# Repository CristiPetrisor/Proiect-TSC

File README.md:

# OpenBook E-Reader - Readme

**Proiect TSC - Caramida-Stoian Petrisor-Cristian**

## Prezentare pe scurt

OpenBook este un e-reader open-source bazat pe ESP32-C6, dotat cu ecran e-paper de 7.5", senzori de mediu, sistem de alimentare cu baterie și conectivitate Wi-Fi și USB-C. Documentul prezintă structura hardware și componentele integrate.

## Diagramă Bloc

```
           +-------------------------+
           |         Battery          |
           +------------+------------+
                        |
                        v
           +-------------------------+
           |     Charging IC (USB-C)  |
           +------------+------------+
                        |
                        v
           +-------------------------+
           |         LDO              |  ---> 3.3V
           +------------+------------+
                        |
     +------------------+-------------------+------------------+
     |                  |                   |                  |
     v                  v                   v                  v
+------------+   +--------------+   +---------------+   +-----------------+
|   ESP32    |<->|    Display   |<->|    BME688     |<->|  Tactile Buttons|
|    -C6     |   |   (SPI: 4W)   |   |   (I2C Bus)   |   |   (GPIO + RC)   |
+------------+   +--------------+   +---------------+   +-----------------+
     |                  ^                    ^                    ^
     |                  |                    |                    |
     |                  |              Pull-up Resistors     Debouncing RC
     |                  |
     v                  |
+----------------------------+
|      USB-C Connector       |
| (USB Data ↔ ESP32 USB)     |
| (ESD & Termination Prot.)  |
+----------------------------+
```

## Lista BOM

| **Componentă**       | **Part Number**               | **Descriere**                          | **Furnizor (Mouser)**                                                               | **Datasheet**                                                                                 |
|----------------------|------------------------------|----------------------------------------|------------------------------------------------------------------------------------|----------------------------------------------------------------------------------------------|
| 1         | ADAFRUIT_LEDCHIP-LED0603           | -       | LED                                       | ADAFRUIT_CHIP-LED0603           | CHG_LED      | [link](https://www.mouser.com/ProductDetail/Adafruit/CHIP-LED0603)               | [datasheet](https://www.mouser.com/datasheet/2/737/CHIP-LED0603-1877199.pdf)       |
| 1         | SJ                                 | -       | SMD solder JUMPER                         | SJ                              | SJ1          | [link](https://www.mouser.com/ProductDetail/TE-Connectivity/1-2176091-2)         | [datasheet](https://www.mouser.com/datasheet/2/418/1-2176091-2-1817091.pdf)        |
| 1         | ESP32_WROVER_EAGLE-LTSPICE_RR0402  | 0.47Ω   | Rezistor                                  | ESP32_WROVER_EAGLE-LTSPICE_R0402| R3           | [link](https://www.mouser.com/ProductDetail/Vishay/CRCW04020047ZRT7)             | [datasheet](https://www.mouser.com/datasheet/2/427/crcwce-1764191.pdf)             |
| 1         | ESP32_WROVER_EAGLE-LTSPICE_RR0402  | 100KΩ   | Rezistor                                  | ESP32_WROVER_EAGLE-LTSPICE_R0402| R1_PWRUSB    | [link](https://www.mouser.com/ProductDetail/Vishay/CRCW0402100KFKED)             | [datasheet](https://www.mouser.com/datasheet/2/427/crcwce-1764191.pdf)             |
| 8         | EAGLE-LTSPICE_CC0402               | 100nF   | Condensator                               | EAGLE-LTSPICE_C0402             | C1, C2, C4_USB, C6, C8, C9, C10, C_DELAY | [link](https://www.mouser.com/ProductDetail/Murata/GRM155R71C104KA88D)            | [datasheet](https://www.mouser.com/datasheet/2/281/GRM155R71C104KA88D-1767201.pdf) |
| 1         | RCL_CPOL-EUCT3528                  | 100µF   | Condensator polarizat                     | RCL_CT3528                      | C3           | [link](https://www.mouser.com/ProductDetail/Panasonic/EEE-FK1V101P)              | [datasheet](https://www.mouser.com/datasheet/2/315/EEE-FK1V101P-1526881.pdf)       |
| 10        | ESP32_WROVER_EAGLE-LTSPICE_RR0402  | 10KΩ    | Rezistor                                  | ESP32_WROVER_EAGLE-LTSPICE_R0402| R1, R1-PINH, R1_PINH1, R2-PINH, R2_PINH1, R4, R_BOOT, R_CHANGE, R_CL1, R_RESET | [link](https://www.mouser.com/ProductDetail/Vishay/CRCW040210K0FKED)              | [datasheet](https://www.mouser.com/datasheet/2/427/crcwce-1764191.pdf)             |
| 6         | ESP32_WROVER_EAGLE-LTSPICE_RR0402  | 10kΩ    | Rezistor                                  | ESP32_WROVER_EAGLE-LTSPICE_R0402| R5, R6, R7, R8, R9, R10 | [link](https://www.mouser.com/ProductDetail/Vishay/CRCW040210K0FKED)              | [datasheet](https://www.mouser.com/datasheet/2/427/crcwce-1764191.pdf)             |
| 1         | EAGLE-LTSPICE_CC0402               | 10µF    | Condensator                               | EAGLE-LTSPICE_C0402             | C7           | [link](https://www.mouser.com/ProductDetail/Murata/GRM155R61A106ME44D)           | [datasheet](https://www.mouser.com/datasheet/2/281/GRM155R61A106ME44D-1767201.pdf) |
| 1         | 112A-TAAR-R03_ATTEND               | -       | Micro SD Card Socket, Push-Push Type      | 112ATAARR03ATTEND               | J4           | [link](https://www.mouser.com/ProductDetail/Attend/112A-TAAR-R03)                | [datasheet](https://www.mouser.com/datasheet/2/828/112A-TAAR-R03-1222862.pdf)      |
| 1         | ESP32_WROVER_EAGLE-LTSPICE_RR0402  | 15Ω     | Rezistor                                  | ESP32_WROVER_EAGLE-LTSPICE_R0402| R_CAPACITOR  | [link](https://www.mouser.com/ProductDetail/Vishay/CRCW040215R0FKED)             | [datasheet](https://www.mouser.com/datasheet/2/427/crcwce-1764191.pdf)             |
| 1         | EAGLE-LTSPICE_CC0402               | 1µF     | Condensator                               | EAGLE-LTSPICE_C0402             | C5           | [link](https://www.mouser.com/ProductDetail/Murata/GRM155R61A105KE15D)           | [datasheet](https://www.mouser.com/datasheet/2/281/GRM155R61A105KE15D-1767201.pdf) |
| 10        | EAGLE-LTSPICE_CC0402               | 1µF/50V | Condensator ceramic multi-strat           | 0402                           | EPD_C1, EPD_C2, EPD_C5, EPD_C6, EPD_C7, EPD_C8, EPD_C9, EPD_C10, EPD_C11, EPD_C12 | [link](https://www.mouser.com/ProductDetail/Murata-Electronics/GRM155R61A105KE15D) | [datasheet](https://www.mouser.com/datasheet/2/281/1/GRM155R61A105KE15_01A-1983730.pdf) |

---

## Detalii Functionalitate Hardware

## ESP32-C6-WROOM-1-N8

- **Rol**: Controler principal, conectivitate wireless și suport periferice.
- **Specificații**: 160MHz, 512KB SRAM, 8MB Flash.
- **Interfețe**:
  - **SPI**: Display e-paper, memorie Flash, card Micro SD.
  - **I2C**: Senzor BME680, monitorizare baterie (MAX17048), RTC (DS3231).
  - **GPIO**: Interacțiune cu butoane și LED-uri.
  - **UART**: Debugging și comunicare serială.

## Senzor BME680

- **Funcționalitate**: Măsoară temperatură, umiditate, presiune atmosferică și calitate aer.
- **Interfață**: I2C la 400kHz.
- **Consum**: Sub 1mA activ, sub 1µA în repaus.

## Sistem de Alimentare

- **Baterie**: Li-Po 2500mAh, 3.7V.
- **Încărcare**: Controlată de MCP73831 prin USB-C, cu capacitate de 1A.
- **Monitorizare**: MAX17048 prin I2C.
- **Consum energetic**:
  - Activ (Wi-Fi + ecran actualizat): ~150mA.
  - Standby (doar ecran afișat): ~10mA.
  - Deep Sleep: Sub 50µA.
  - **Autonomie estimată**: Aproximativ o săptămână (~250 ore cu un consum mediu de 10mA).

## Display E-Paper
  
-Dimensiune: 7.5 inch, cu o rezoluție de 800x480 pixeli și un contrast de 8:1.
-Conectivitate: Se conectează prin interfața SPI și are linii dedicate pentru control și resetare.
-Consum de energie: Sub 50mA în timpul actualizării imaginii și aproape zero în modul standby.

## Butoane de Navigare

- Butoane tactile Panasonic EVQPUJ02K cu rezistență pull-up de 10KΩ.

## USB-C

- **Rol**: Încărcare (5V/1A) și transfer de date (USB 2.0).
- **Protecție**: Diode ESD (USBLC6-2SC6Y) pentru siguranță la supratensiune.

## Configurare Pini ESP32-C6

| **Pin ESP32-C6** | **Funcție**         | **Componentă**         | **Rol**                                    |
|------------------|--------------------|------------------------|--------------------------------------------|
| GPIO0           | BOOT_BUTTON        | Buton                  | Mod boot la inițializare                   |
| GPIO1           | RESET_BUTTON       | Buton                  | Reset manual                               |
| GPIO2           | CHANGE_BUTTON      | Buton                  | Schimbare meniuri                          |
| GPIO3           | EPD_CS             | Display E-Paper        | Chip Select pentru SPI                     |
| GPIO4           | EPD_DC             | Display E-Paper        | Control Date/Comenzi                       |
| GPIO5           | EPD_RST            | Display E-Paper        | Reset display                              |
| GPIO6           | EPD_BUSY           | Display E-Paper        | Detectare stare refresh                    |
| GPIO7           | SPI_MOSI           | Display, Flash, SD     | Linii de date SPI                          |
| GPIO8           | SPI_MISO           | Display, Flash, SD     | Linie de date SPI (citire)                 |
| GPIO9           | SPI_SCK            | Display, Flash, SD     | Semnal de ceas SPI                         |
| GPIO10          | FLASH_CS           | Memorie Flash          | Chip Select pentru memorie                 |
| GPIO11          | SD_CS              | Card Micro SD          | Chip Select pentru card SD                 |
| GPIO12          | I2C_SDA            | BME680, MAX17048, DS3231 | Linie de date pentru I2C                   |
| GPIO13          | I2C_SCL            | BME680, MAX17048, DS3231 | Linie de ceas pentru I2C                   |
| GPIO14          | CHG_LED            | LED                    | Indică procesul de încărcare               |
| GPIO15          | UART_TX            | Debugging              | Transmitere date seriale                    |
| GPIO16          | UART_RX            | Debugging              | Recepție date seriale                       |
| GPIO17          | USB_D+             | USB-C                  | Linie de date USB pozitivă                  |
| GPIO18          | USB_D-             | USB-C                  | Linie de date USB negativă                  |

Notă: Pinii sunt alocați conform specificațiilor ESP32-C6 și cerințelor dispozitivului OpenBook. Anumiți pini sunt multifuncționali și pot fi utilizați în diferite configurații.

Poze Schematic si PCB

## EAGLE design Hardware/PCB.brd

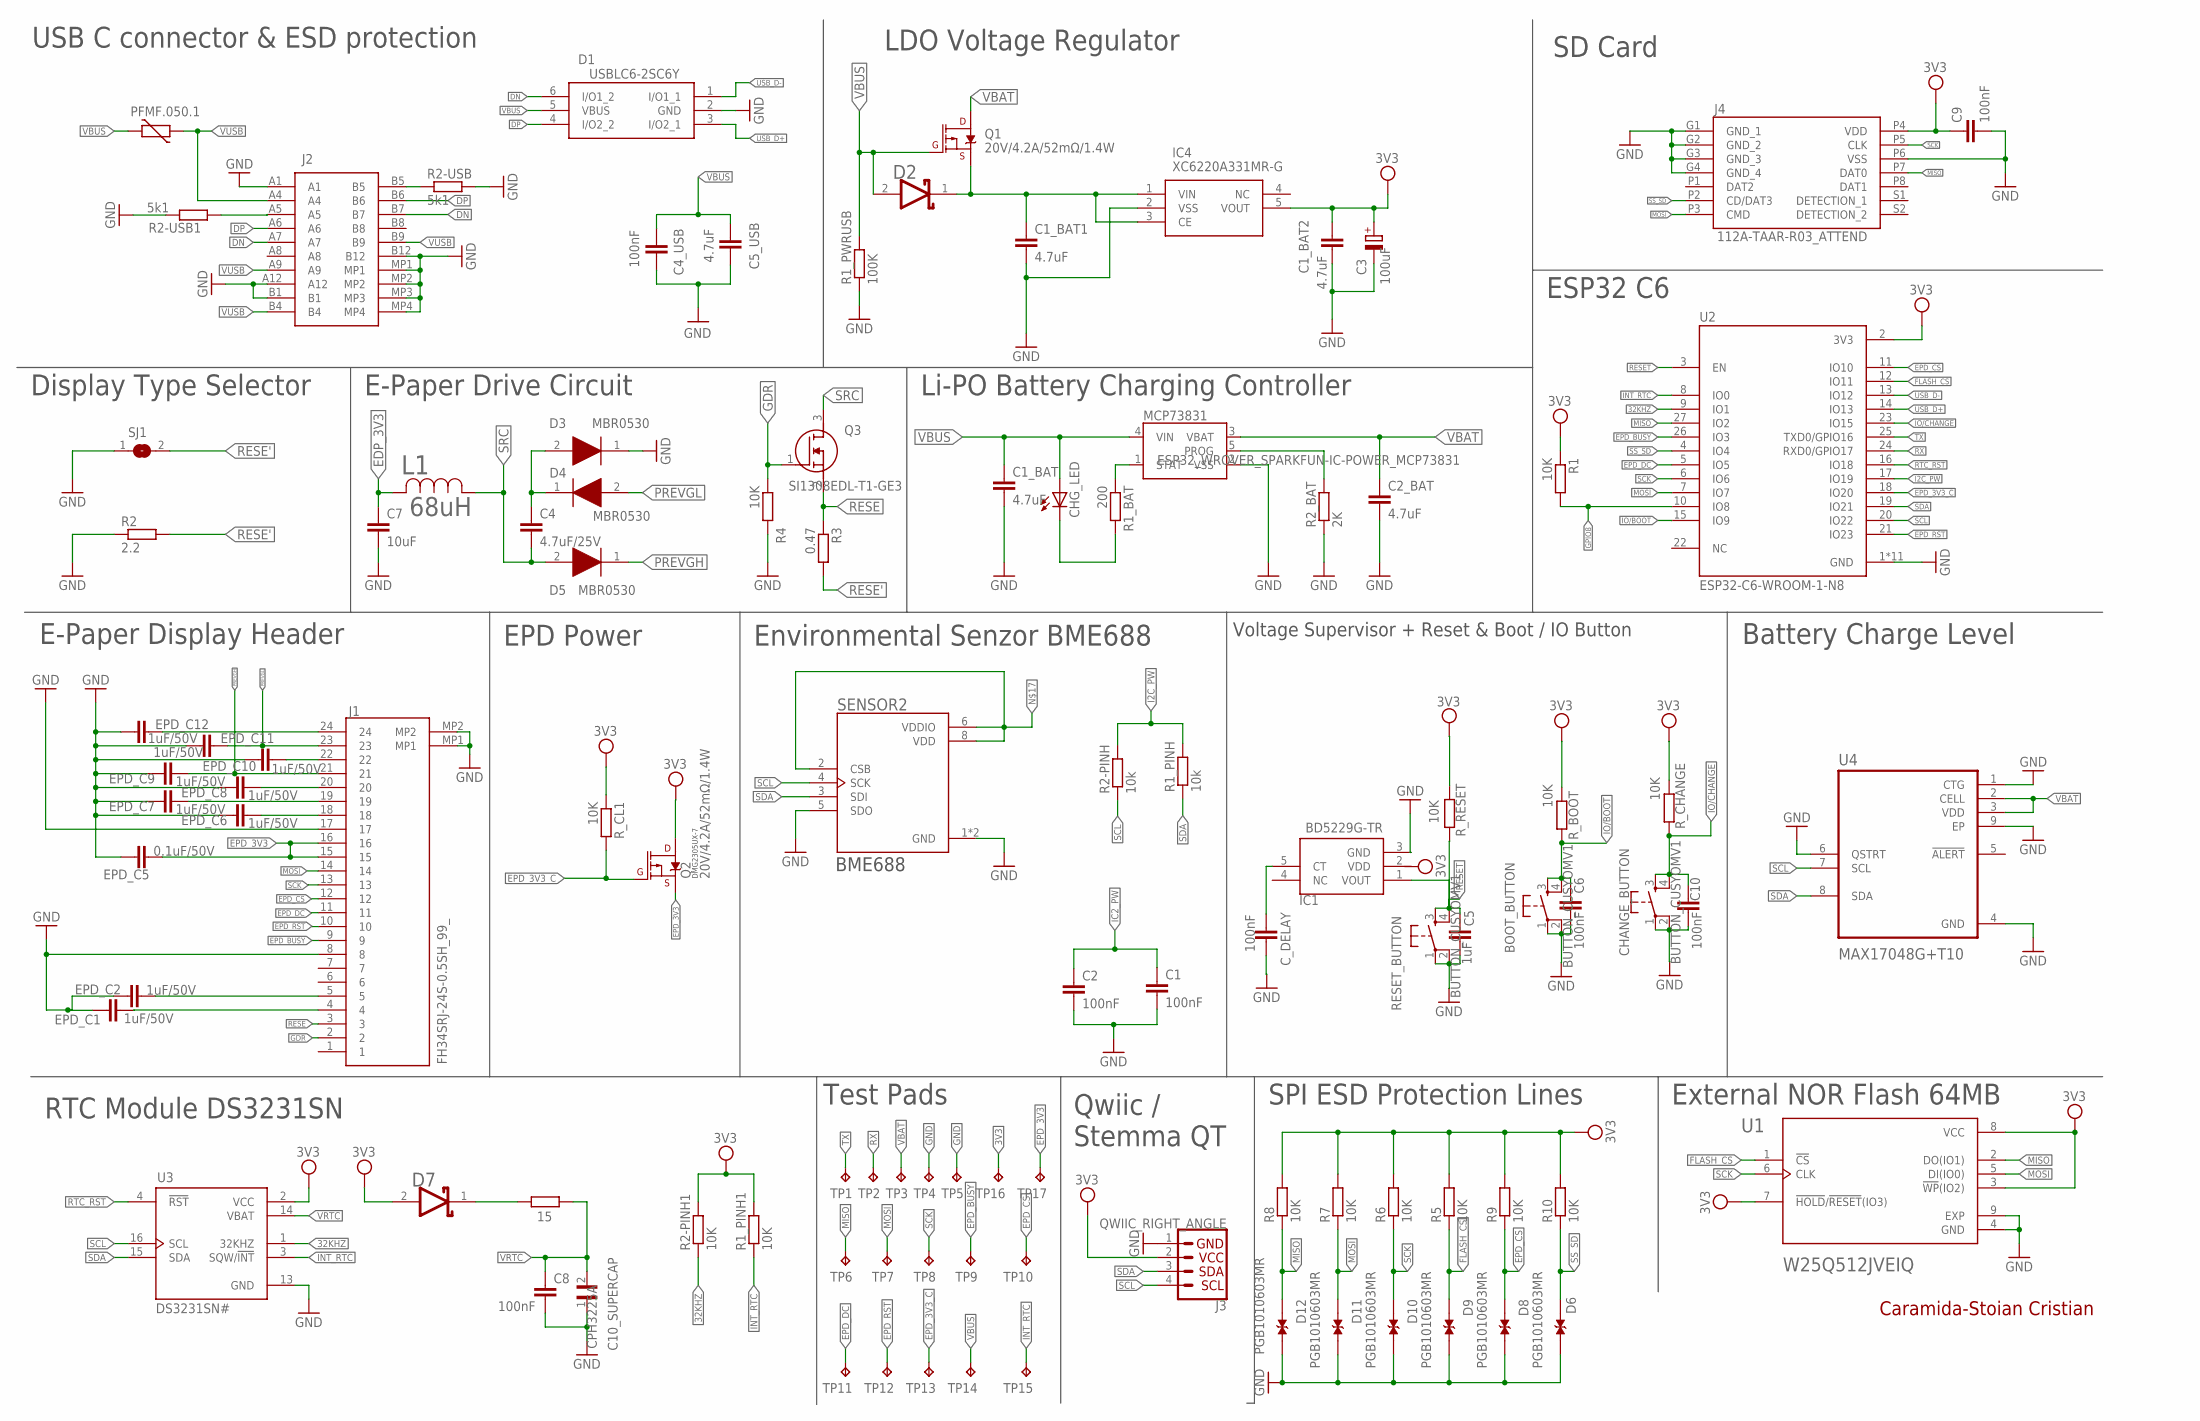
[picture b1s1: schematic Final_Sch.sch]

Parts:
BOOT_BUTTON: BUTTON_CUSYOMV1; MYBUTTON
C1, C2, C4_USB, C8, C9: 100nF; ESP32_WROVER_EAGLE-LTSPICE_C0402
C1_BAT, C1_BAT1, C1_BAT2, C2_BAT, C5_USB: 4.7uF; ESP32_WROVER_EAGLE-LTSPICE_C0402
C3: 100uF; RCL_CT3528
C4: 4.7uF/25V; ESP32_WROVER_EAGLE-LTSPICE_C0402
C5: 1uF; EAGLE-LTSPICE_C0402
C6, C10: 100nF; EAGLE-LTSPICE_C0402
C7: 10uF; ESP32_WROVER_EAGLE-LTSPICE_C0402
C10_SUPERCAP: CPH3225A; CAPCP3225X100N
CHANGE_BUTTON: BUTTON_CUSYOMV1; MYBUTTON
CHG_LED: ADAFRUIT_LEDCHIP-LED0603; ADAFRUIT_CHIP-LED0603
C_DELAY: 100nF; ESP32_WROVER_EAGLE-LTSPICE_C0402
D1: USBLC6-2SC6Y; SOT95P280X145-6N
D2, D7: ESP32_WROVER_AVX---SD0805S020S1R0_AVX_SD0805S020S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; ESP32_WROVER_AVX---SD0805S020S1R0_AVX_SD0805S020S1R0_0
D3, D4, D5: MBR0530; SOD3716X135N
D6, D8, D9, D10, D11, D12: PGB1010603MR; DIOC1608X36N
EPD_C1, EPD_C2, EPD_C6, EPD_C7, EPD_C8, EPD_C9, EPD_C10, EPD_C11, EPD_C12: 1uF/50V; EAGLE-LTSPICE_C0402
EPD_C5: 0.1uF/50V; EAGLE-LTSPICE_C0402
IC1: BD5229G-TR; SOT95P280X125-5N
IC4: XC6220A331MR-G; SOT95P280X120-5N
J1: FH34SRJ-24S-0.5SH_99_; FH34SRJ24S05SH99
J2: SAMACSYS_PARTS_USB4110-GF-A; SAMACSYS_PARTS_USB4110GFA
J3: QWIIC_RIGHT_ANGLE; JST04_1MM_RA
J4: 112A-TAAR-R03_ATTEND; 112ATAARR03ATTEND
L1: 68uH; IND_4828-WE-TPC_WRE
MCP73831: ESP32_WROVER_SPARKFUN-IC-POWER_MCP73831; ESP32_WROVER_SPARKFUN-IC-POWER_SOT23-5
PFMF.050.1: ESP32C6_VARISTORCN1812; ESP32C6_VARISTOR_CT/CN1812
Q1, Q2: 20V/4.2A/52mΩ/1.4W; ESP32_WROVER_SPARKFUN-DISCRETESEMI_SOT23-3
Q3: SI1308EDL-T1-GE3; SOT65P210X110-3N
R1, R1_PINH1, R2-PINH1, R4, R5, R6, R7, R8, R9, R10: 10K; ESP32_WROVER_EAGLE-LTSPICE_R0402
R1_BAT: 200; ESP32_WROVER_EAGLE-LTSPICE_R0402
R1_PINH, R2-PINH: 10k; ESP32_WROVER_EAGLE-LTSPICE_R0402
R1_PWRUSB: 100K; ESP32_WROVER_EAGLE-LTSPICE_R0402
R2: 2.2; ESP32_WROVER_EAGLE-LTSPICE_R0402
R2-USB, R2-USB1: 5k1; ESP32_WROVER_EAGLE-LTSPICE_R0402
R2_BAT: 2K; ESP32_WROVER_EAGLE-LTSPICE_R0402
R3: 0.47; ESP32_WROVER_EAGLE-LTSPICE_R0402
RESET_BUTTON: BUTTON_CUSYOMV1; MYBUTTON
R_BOOT: 10K; ESP32_WROVER_EAGLE-LTSPICE_R0402
R_CAPACITOR: 15; ESP32_WROVER_EAGLE-LTSPICE_R0402
R_CHANGE: 10K; ESP32_WROVER_EAGLE-LTSPICE_R0402
R_CL1: 10K; ESP32_WROVER_EAGLE-LTSPICE_R0402
R_RESET: 10K; ESP32_WROVER_EAGLE-LTSPICE_R0402
SENSOR2: ESP32_WROVER_BME680_BME680; ESP32_WROVER_BME680_PSON80P300X300X100-8N
SJ1: SJ
TP1, TP2, TP3, TP4, TP5, TP6, TP7, TP8, TP9, TP10, TP11, TP12, TP13, TP14, TP15, TP16, TP17: TPTP20R; TP20R
U1: W25Q512JVEIQ; SON127P600X800X80-9N
U2: ESP32-C6-WROOM-1-N8; XCVR_ESP32-C6-WROOM-1-N8
U3: DS3231SN#; SOIC127P1032X265-16N
U4: MAX17048G+T10; SON50P200X200X80-9N

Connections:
3V3: C1_BAT2.1, C3.+, C9.1, D7.2 (ANODE), IC4.5 (VOUT), J3.2, J4.P4 (VDD), Q2.3 (D), R1.1, R1_PINH1.2, R2-PINH1.2, R5.2, R6.2, R7.2, R8.2, R9.2, R10.2, R_BOOT.2, R_CHANGE.2, R_CL1.1, R_RESET.2, TP16.TP, U1.3 (!WP!(IO2)), U1.7 (!HOLD!/!RESET!(IO3)), U1.8 (VCC), U2.2 (3V3), U3.2 (VCC)
32KHZ: R2-PINH1.1, U2.9 (IO1), U3.1 (32KHZ)
DN: D1.6 (I/O1_2), J2.A7, J2.B7
DP: D1.4 (I/O2_2), J2.A6, J2.B6
EDP_3V3: C7.1, L1.2
EPD_3V3: EPD_C5.2, J1.15, J1.16, Q2.2 (S), TP17.TP
EPD_3V3_C: Q2.1 (G), R_CL1.2, TP13.TP, U2.18 (IO20)
EPD_BUSY: J1.9, TP9.TP, U2.26 (IO3)
EPD_CS: D8.1, J1.12, R9.1, TP10.TP, U2.11 (IO10)
EPD_DC: J1.11, TP11.TP, U2.5 (IO5)
EPD_RST: J1.10, TP12.TP, U2.21 (IO23)
FLASH_CS: D9.1, R5.1, U1.1 (!CS), U2.12 (IO11)
GDR: J1.2, Q3.1 (G), R4.1
GND: BOOT_BUTTON.1, BOOT_BUTTON.2, C1.2, C1_BAT.2, C1_BAT1.2, C1_BAT2.2, C2.2, C2_BAT.2, C3.-, C4_USB.2, C5.2, C5_USB.2, C6.2, C7.2, C8.2, C9.2, C10.2, C10_SUPERCAP.1, CHANGE_BUTTON.1, CHANGE_BUTTON.2, C_DELAY.2, D1.2 (GND), D3.1 (K), D6.2, D8.2, D9.2, D10.2, D11.2, D12.2, EPD_C1.1, EPD_C2.1, EPD_C5.1, EPD_C6.1, EPD_C7.1, EPD_C8.1, EPD_C9.1, EPD_C10.1, EPD_C11.1, EPD_C12.1, IC1.3 (GND), IC4.2 (VSS), J1.8, J1.17, J1.MP1, J1.MP2, J2.A1, J2.A12, J2.B1, J2.B12, J2.MP1, J2.MP2, J2.MP3, J2.MP4, J3.1, J4.G1 (GND_1), J4.G2 (GND_2), J4.G3 (GND_3), J4.G4 (GND_4), J4.P6 (VSS), MCP73831.2 (VSS), R1_PWRUSB.1, R2.1, R2-USB.2, R2-USB1.1, R2_BAT.1, R4.2, RESET_BUTTON.1, RESET_BUTTON.2, SENSOR2.1 (GND), SENSOR2.5 (SDO), SENSOR2.7 (GND), SJ1.1, TP4.TP, TP5.TP, U1.4 (GND), U1.9 (EXP), U2.1 (GND), U2.28 (GND), U2.29_1 (GND), U2.29_2 (GND), U2.29_3 (GND), U2.29_4 (GND), U2.29_5 (GND), U2.29_6 (GND), U2.29_7 (GND), U2.29_8 (GND), U2.29_9 (GND), U3.13 (GND), U4.1 (CTG), U4.4 (GND), U4.6 (QSTRT), U4.9 (EP)
GPIO8: R1.2, U2.10 (IO8)
I2C_PW: R1_PINH.2, R2-PINH.2, U2.17 (IO19)
IC2_PW: C1.1, C2.1
INT_RTC: R1_PINH1.1, TP15.TP, U2.8 (IO0), U3.3 (SQW/!INT)
IO/BOOT: BOOT_BUTTON.3, BOOT_BUTTON.4, C6.1, R_BOOT.1, U2.15 (IO9)
IO/CHANGE: C10.1, CHANGE_BUTTON.3, CHANGE_BUTTON.4, R_CHANGE.1, U2.23 (IO15)
MISO: D12.1, J4.P7 (DAT0), R8.1, TP6.TP, U1.2 (DO(IO1)), U2.27 (IO2)
MOSI: D11.1, J1.14, J4.P3 (CMD), R7.1, TP7.TP, U1.5 (DI(IO0)), U2.7 (IO7)
unnamed: EPD_C10.2, J1.22
unnamed: C1_BAT1.1, D2.1 (CATHODE), IC4.1 (VIN), IC4.3 (CE), Q1.2 (S)
unnamed: MCP73831.5 (PROG), R2_BAT.2
unnamed: EPD_C8.2, J1.20
unnamed: J2.B5, R2-USB.1
unnamed: C4.1, D3.2 (A), D4.1 (K)
unnamed: MCP73831.1 (STAT), R1_BAT.1
unnamed: CHG_LED.C, R1_BAT.2
unnamed: EPD_C7.2, J1.19
unnamed: J2.A5, R2-USB1.2
unnamed: EPD_C6.2, J1.18
unnamed: EPD_C12.2, J1.24
unnamed: D7.1 (CATHODE), R_CAPACITOR.2
unnamed: EPD_C2.2, J1.5
unnamed: EPD_C1.2, J1.4
unnamed: SENSOR2.2 (CSB), SENSOR2.6 (VDDIO), SENSOR2.8 (VDD)
unnamed: C_DELAY.1, IC1.5 (CT)
PREVGH: D5.1 (K), EPD_C9.2, J1.21
PREVGL: D4.2 (A), EPD_C11.2, J1.23
RESE: J1.3, Q3.2 (S), R3.1
RESE': R2.2, R3.2, SJ1.2
RESET: C5.1, IC1.1 (VOUT), RESET_BUTTON.3, RESET_BUTTON.4, R_RESET.1, U2.3 (EN)
RTC_RST: U2.16 (IO18), U3.4 (!RST)
RX: TP2.TP, U2.24 (RXD0/GPIO17)
SCK: D10.1, J1.13, J4.P5 (CLK), R6.1, TP8.TP, U1.6 (CLK), U2.6 (IO6)
SCL: J3.4, R2-PINH.1, SENSOR2.4 (SCK), U2.20 (IO22), U3.16 (SCL), U4.7 (SCL)
SDA: J3.3, R1_PINH.1, SENSOR2.3 (SDI), U2.19 (IO21), U3.15 (SDA), U4.8 (SDA)
SRC: C4.2, D5.2 (A), L1.1, Q3.3 (D)
SS_SD: D6.1, J4.P2 (CD/DAT3), R10.1, U2.4 (IO4)
TX: TP1.TP, U2.25 (TXD0/GPIO16)
USB_D+: D1.3 (I/O2_1), U2.14 (IO13)
USB_D-: D1.1 (I/O1_1), U2.13 (IO12)
VBAT: C2_BAT.1, MCP73831.3 (VBAT), Q1.3 (D), TP3.TP, U4.2 (CELL), U4.3 (VDD)
VBUS: C1_BAT.1, C4_USB.1, C5_USB.1, CHG_LED.A, D1.5 (VBUS), D2.2 (ANODE), MCP73831.4 (VIN), PFMF.050.1.2, Q1.1 (G), R1_PWRUSB.2, TP14.TP
VRTC: C8.1, C10_SUPERCAP.2, R_CAPACITOR.1, U3.14 (VBAT)
VUSB: J2.A4, J2.A9, J2.B4, J2.B9, PFMF.050.1.1

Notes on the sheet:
USB C connector & ESD protection
LDO Voltage Regulator
SD Card
ESP32 C6
Li-PO Battery Charging Controller
Display Type Selector
E-Paper Drive Circuit
Battery Charge Level
External NOR Flash 64MB
E-Paper Display Header
DMG2305UX-7
EPD Power
Environmental Senzor BME688
RTC Module DS3231SN
Qwiic / Stemma QT
Test Pads
SPI ESD Protection Lines
Voltage Supervisor + Reset & Boot / IO Button
BME688
Caramida-Stoian Cristian

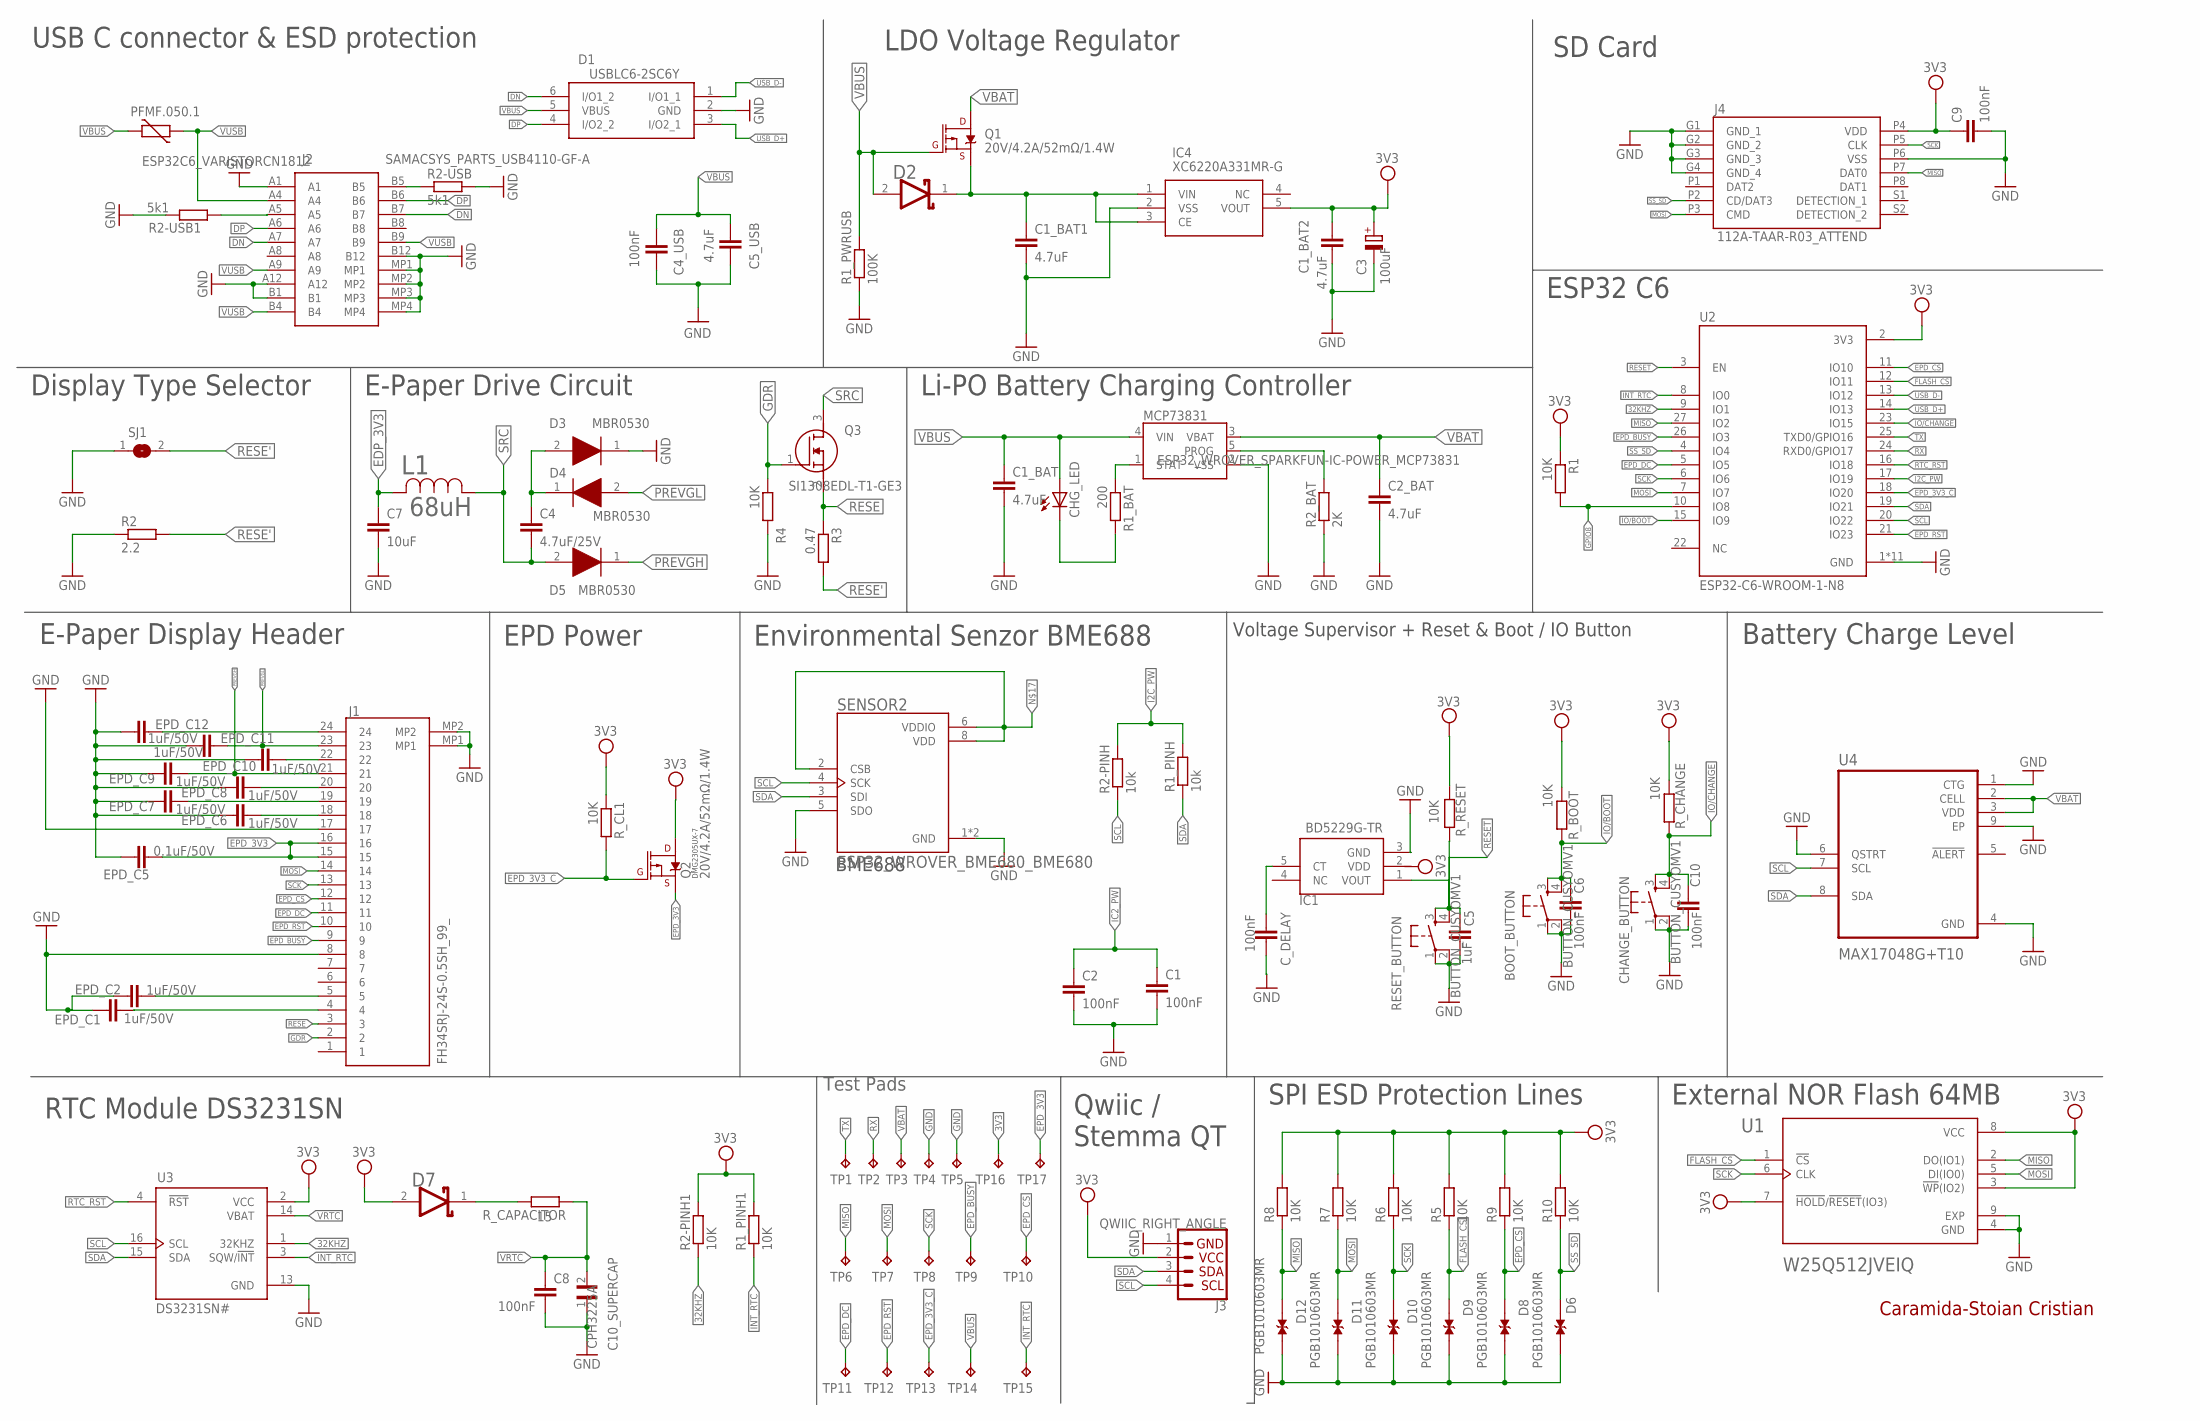
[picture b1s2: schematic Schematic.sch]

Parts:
BOOT_BUTTON: BUTTON_CUSYOMV1; MYBUTTON
C1, C2, C4_USB, C6, C8, C9, C10: 100nF; ESP32_WROVER_EAGLE-LTSPICE_C0402
C1_BAT, C1_BAT1, C1_BAT2, C2_BAT, C5_USB: 4.7uF; ESP32_WROVER_EAGLE-LTSPICE_C0402
C3: 100uF; RCL_CT3528
C4: 4.7uF/25V; ESP32_WROVER_EAGLE-LTSPICE_C0402
C5: 1uF; ESP32_WROVER_EAGLE-LTSPICE_C0402
C7: 10uF; ESP32_WROVER_EAGLE-LTSPICE_C0402
C10_SUPERCAP: CPH3225A; CAPCP3225X100N
CHANGE_BUTTON: BUTTON_CUSYOMV1; MYBUTTON
CHG_LED: ADAFRUIT_LEDCHIP-LED0603; ADAFRUIT_CHIP-LED0603
C_DELAY: 100nF; ESP32_WROVER_EAGLE-LTSPICE_C0402
D1: USBLC6-2SC6Y; SOT95P280X145-6N
D2, D7: ESP32_WROVER_AVX---SD0805S020S1R0_AVX_SD0805S020S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; ESP32_WROVER_AVX---SD0805S020S1R0_AVX_SD0805S020S1R0_0
D3, D4, D5: MBR0530; SOD3716X135N
D6, D8, D9, D10, D11, D12: PGB1010603MR; DIOC1608X36N
EPD_C1, EPD_C2, EPD_C6, EPD_C7, EPD_C8, EPD_C9, EPD_C10, EPD_C11, EPD_C12: 1uF/50V; ESP32_WROVER_EAGLE-LTSPICE_C0402
EPD_C5: 0.1uF/50V; ESP32_WROVER_EAGLE-LTSPICE_C0402
IC1: BD5229G-TR; SOT95P280X125-5N
IC4: XC6220A331MR-G; ESP32_WROVER_SPARKFUN-IC-POWER_SOT23-5
J1: FH34SRJ-24S-0.5SH_99_; FH34SRJ24S05SH99
J2: SAMACSYS_PARTS_USB4110-GF-A; SAMACSYS_PARTS_USB4110GFA
J3: QWIIC_RIGHT_ANGLE; JST04_1MM_RA
J4: 112A-TAAR-R03_ATTEND; 112ATAARR03ATTEND
L1: 68uH; IND_4828-WE-TPC_WRE
MCP73831: ESP32_WROVER_SPARKFUN-IC-POWER_MCP73831; ESP32_WROVER_SPARKFUN-IC-POWER_SOT23-5
PFMF.050.1: ESP32C6_VARISTORCN1812; ESP32C6_VARISTOR_CT/CN1812
Q1, Q2: 20V/4.2A/52mΩ/1.4W; ESP32_WROVER_SPARKFUN-DISCRETESEMI_SOT23-3
Q3: SI1308EDL-T1-GE3; SOT65P210X110-3N
R1, R1_PINH1, R2-PINH1, R4, R5, R6, R7, R8, R9, R10: 10K; ESP32_WROVER_EAGLE-LTSPICE_R0402
R1_BAT: 200; ESP32_WROVER_EAGLE-LTSPICE_R0402
R1_PINH, R2-PINH: 10k; ESP32_WROVER_EAGLE-LTSPICE_R0402
R1_PWRUSB: 100K; ESP32_WROVER_EAGLE-LTSPICE_R0402
R2: 2.2; ESP32_WROVER_EAGLE-LTSPICE_R0402
R2-USB, R2-USB1: 5k1; ESP32_WROVER_EAGLE-LTSPICE_R0402
R2_BAT: 2K; ESP32_WROVER_EAGLE-LTSPICE_R0402
R3: 0.47; ESP32_WROVER_EAGLE-LTSPICE_R0402
RESET_BUTTON: BUTTON_CUSYOMV1; MYBUTTON
R_BOOT: 10K; ESP32_WROVER_EAGLE-LTSPICE_R0402
R_CAPACITOR: 15; ESP32_WROVER_EAGLE-LTSPICE_R0402
R_CHANGE: 10K; ESP32_WROVER_EAGLE-LTSPICE_R0402
R_CL1: 10K; ESP32_WROVER_EAGLE-LTSPICE_R0402
R_RESET: 10K; ESP32_WROVER_EAGLE-LTSPICE_R0402
SENSOR2: ESP32_WROVER_BME680_BME680; ESP32_WROVER_BME680_PSON80P300X300X100-8N
SJ1: SJ; SOT65P210X110-3N
TP1, TP2, TP3, TP4, TP5, TP6, TP7, TP8, TP9, TP10, TP11, TP12, TP13, TP14, TP15, TP16, TP17: TPTP20R; TP20R
U1: W25Q512JVEIQ; SON127P600X800X80-9N
U2: ESP32-C6-WROOM-1-N8; XCVR_ESP32-C6-WROOM-1-N8
U3: DS3231SN#; SOIC127P1032X265-16N
U4: MAX17048G+T10; SON50P200X200X80-9N

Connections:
3V3: C1_BAT2.1, C3.+, C9.1, D7.2 (ANODE), IC4.5 (VOUT), J3.2, J4.P4 (VDD), Q2.3 (D), R1.1, R1_PINH1.2, R2-PINH1.2, R5.2, R6.2, R7.2, R8.2, R9.2, R10.2, R_BOOT.2, R_CHANGE.2, R_CL1.1, R_RESET.2, TP16.TP, U1.3 (!WP!(IO2)), U1.7 (!HOLD!/!RESET!(IO3)), U1.8 (VCC), U2.2 (3V3), U3.2 (VCC)
32KHZ: R2-PINH1.1, U2.9 (IO1), U3.1 (32KHZ)
DN: D1.6 (I/O1_2), J2.A7, J2.B7
DP: D1.4 (I/O2_2), J2.A6, J2.B6
EDP_3V3: C7.1, L1.2
EPD_3V3: EPD_C5.2, J1.15, J1.16, Q2.2 (S), TP17.TP
EPD_3V3_C: Q2.1 (G), R_CL1.2, TP13.TP, U2.18 (IO20)
EPD_BUSY: J1.9, TP9.TP, U2.26 (IO3)
EPD_CS: D8.1, J1.12, R9.1, TP10.TP, U2.11 (IO10)
EPD_DC: J1.11, TP11.TP, U2.5 (IO5)
EPD_RST: J1.10, TP12.TP, U2.21 (IO23)
FLASH_CS: D9.1, R5.1, U1.1 (!CS), U2.12 (IO11)
GDR: J1.2, Q3.1 (G), R4.1
GND: BOOT_BUTTON.1, BOOT_BUTTON.2, C1.2, C1_BAT.2, C1_BAT1.2, C1_BAT2.2, C2.2, C2_BAT.2, C3.-, C4_USB.2, C5.2, C5_USB.2, C6.2, C7.2, C8.2, C9.2, C10.2, C10_SUPERCAP.1, CHANGE_BUTTON.1, CHANGE_BUTTON.2, C_DELAY.2, D1.2 (GND), D3.1 (K), D6.2, D8.2, D9.2, D10.2, D11.2, D12.2, EPD_C1.1, EPD_C2.1, EPD_C5.1, EPD_C6.1, EPD_C7.1, EPD_C8.1, EPD_C9.1, EPD_C10.1, EPD_C11.1, EPD_C12.1, IC1.3 (GND), IC4.2 (VSS), J1.8, J1.17, J1.MP1, J1.MP2, J2.A1, J2.A12, J2.B1, J2.B12, J2.MP1, J2.MP2, J2.MP3, J2.MP4, J3.1, J4.G1 (GND_1), J4.G2 (GND_2), J4.G3 (GND_3), J4.G4 (GND_4), J4.P6 (VSS), MCP73831.2 (VSS), R1_PWRUSB.1, R2.1, R2-USB.2, R2-USB1.1, R2_BAT.1, R4.2, RESET_BUTTON.1, RESET_BUTTON.2, SENSOR2.1 (GND), SENSOR2.5 (SDO), SENSOR2.7 (GND), SJ1.1, TP4.TP, TP5.TP, U1.4 (GND), U1.9 (EXP), U2.1 (GND), U2.28 (GND), U2.29_1 (GND), U2.29_2 (GND), U2.29_3 (GND), U2.29_4 (GND), U2.29_5 (GND), U2.29_6 (GND), U2.29_7 (GND), U2.29_8 (GND), U2.29_9 (GND), U3.13 (GND), U4.1 (CTG), U4.4 (GND), U4.6 (QSTRT), U4.9 (EP)
GPIO8: R1.2, U2.10 (IO8)
I2C_PW: R1_PINH.2, R2-PINH.2, U2.17 (IO19)
IC2_PW: C1.1, C2.1
INT_RTC: R1_PINH1.1, TP15.TP, U2.8 (IO0), U3.3 (SQW/!INT)
IO/BOOT: BOOT_BUTTON.3, BOOT_BUTTON.4, C6.1, R_BOOT.1, U2.15 (IO9)
IO/CHANGE: C10.1, CHANGE_BUTTON.3, CHANGE_BUTTON.4, R_CHANGE.1, U2.23 (IO15)
MISO: D12.1, J4.P7 (DAT0), R8.1, TP6.TP, U1.2 (DO(IO1)), U2.27 (IO2)
MOSI: D11.1, J1.14, J4.P3 (CMD), R7.1, TP7.TP, U1.5 (DI(IO0)), U2.7 (IO7)
unnamed: EPD_C10.2, J1.22
unnamed: C1_BAT1.1, D2.1 (CATHODE), IC4.1 (VIN), IC4.3 (CE), Q1.2 (S)
unnamed: MCP73831.5 (PROG), R2_BAT.2
unnamed: EPD_C8.2, J1.20
unnamed: J2.B5, R2-USB.1
unnamed: C4.1, D3.2 (A), D4.1 (K)
unnamed: MCP73831.1 (STAT), R1_BAT.1
unnamed: CHG_LED.C, R1_BAT.2
unnamed: EPD_C7.2, J1.19
unnamed: J2.A5, R2-USB1.2
unnamed: EPD_C6.2, J1.18
unnamed: EPD_C12.2, J1.24
unnamed: D7.1 (CATHODE), R_CAPACITOR.2
unnamed: EPD_C2.2, J1.5
unnamed: EPD_C1.2, J1.4
unnamed: SENSOR2.2 (CSB), SENSOR2.6 (VDDIO), SENSOR2.8 (VDD)
unnamed: C_DELAY.1, IC1.5 (CT)
PREVGH: D5.1 (K), EPD_C9.2, J1.21
PREVGL: D4.2 (A), EPD_C11.2, J1.23
RESE: J1.3, Q3.2 (S), R3.1
RESE': R2.2, R3.2, SJ1.2
RESET: C5.1, IC1.1 (VOUT), RESET_BUTTON.3, RESET_BUTTON.4, R_RESET.1, U2.3 (EN)
RTC_RST: U2.16 (IO18), U3.4 (!RST)
RX: TP2.TP, U2.24 (RXD0/GPIO17)
SCK: D10.1, J1.13, J4.P5 (CLK), R6.1, TP8.TP, U1.6 (CLK), U2.6 (IO6)
SCL: J3.4, R2-PINH.1, SENSOR2.4 (SCK), U2.20 (IO22), U3.16 (SCL), U4.7 (SCL)
SDA: J3.3, R1_PINH.1, SENSOR2.3 (SDI), U2.19 (IO21), U3.15 (SDA), U4.8 (SDA)
SRC: C4.2, D5.2 (A), L1.1, Q3.3 (D)
SS_SD: D6.1, J4.P2 (CD/DAT3), R10.1, U2.4 (IO4)
TX: TP1.TP, U2.25 (TXD0/GPIO16)
USB_D+: D1.3 (I/O2_1), U2.14 (IO13)
USB_D-: D1.1 (I/O1_1), U2.13 (IO12)
VBAT: C2_BAT.1, MCP73831.3 (VBAT), Q1.3 (D), TP3.TP, U4.2 (CELL), U4.3 (VDD)
VBUS: C1_BAT.1, C4_USB.1, C5_USB.1, CHG_LED.A, D1.5 (VBUS), D2.2 (ANODE), MCP73831.4 (VIN), PFMF.050.1.2, Q1.1 (G), R1_PWRUSB.2, TP14.TP
VRTC: C8.1, C10_SUPERCAP.2, R_CAPACITOR.1, U3.14 (VBAT)
VUSB: J2.A4, J2.A9, J2.B4, J2.B9, PFMF.050.1.1

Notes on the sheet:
USB C connector & ESD protection
LDO Voltage Regulator
SD Card
ESP32 C6
Li-PO Battery Charging Controller
Display Type Selector
E-Paper Drive Circuit
Battery Charge Level
External NOR Flash 64MB
E-Paper Display Header
DMG2305UX-7
EPD Power
Environmental Senzor BME688
RTC Module DS3231SN
Qwiic / Stemma QT
SPI ESD Protection Lines
Voltage Supervisor + Reset & Boot / IO Button
BME688
Caramida-Stoian Cristian
Test Pads

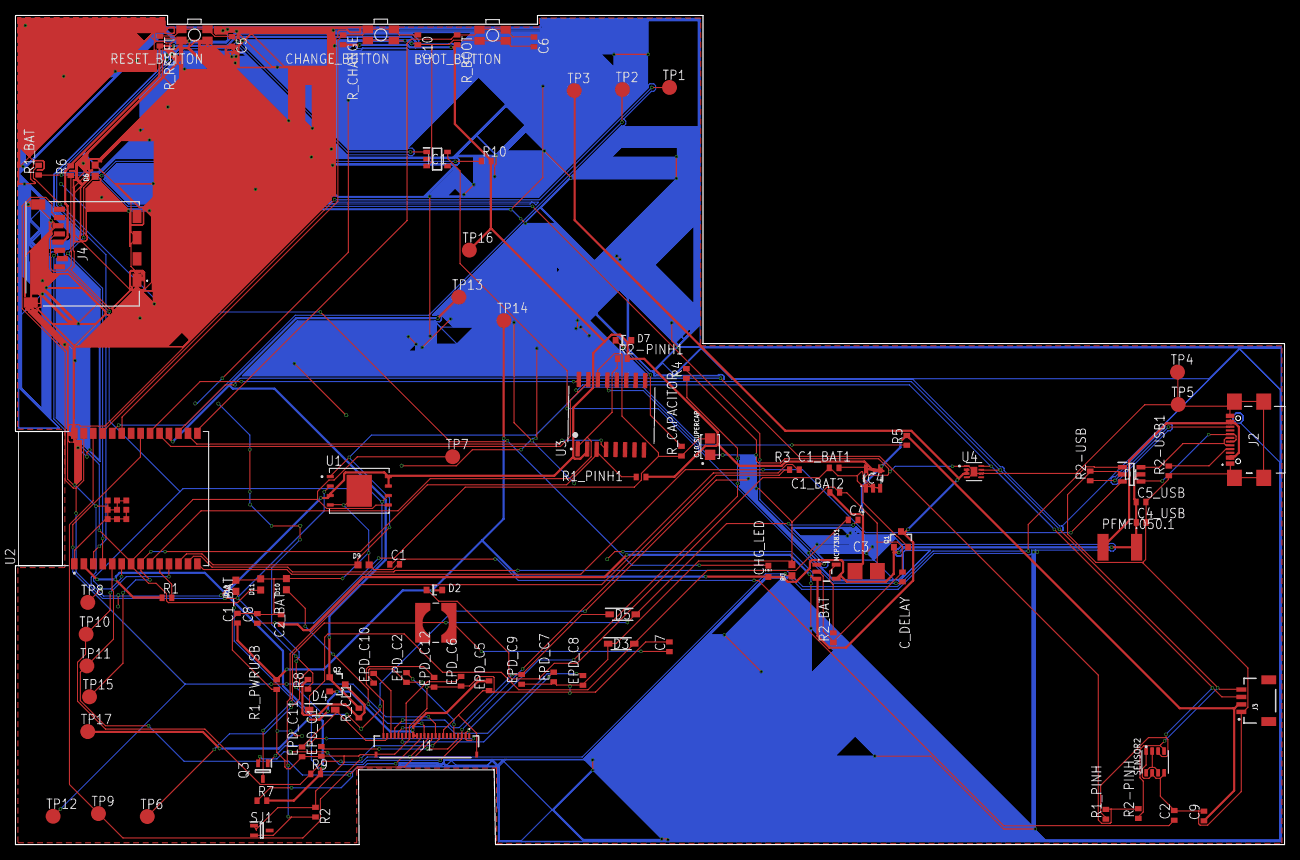
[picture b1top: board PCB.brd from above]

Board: 2 copper layers, 170.2 x 111.2 mm, 103 parts (0 on the bottom side), 58 nets.

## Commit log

2025-04-06 Update README.md
    Update
2025-04-06 Create LICENSE
2025-04-10 Update README.md
    eroare formatare
2025-04-15 Add files via upload
    Am adăugat imaginile pt 3d

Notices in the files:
parts and their libraries:
DeskAssistant v19 v1: COPYRIGHT: Copyright (C) 2024 Ultra Librarian. All rights reserved.
